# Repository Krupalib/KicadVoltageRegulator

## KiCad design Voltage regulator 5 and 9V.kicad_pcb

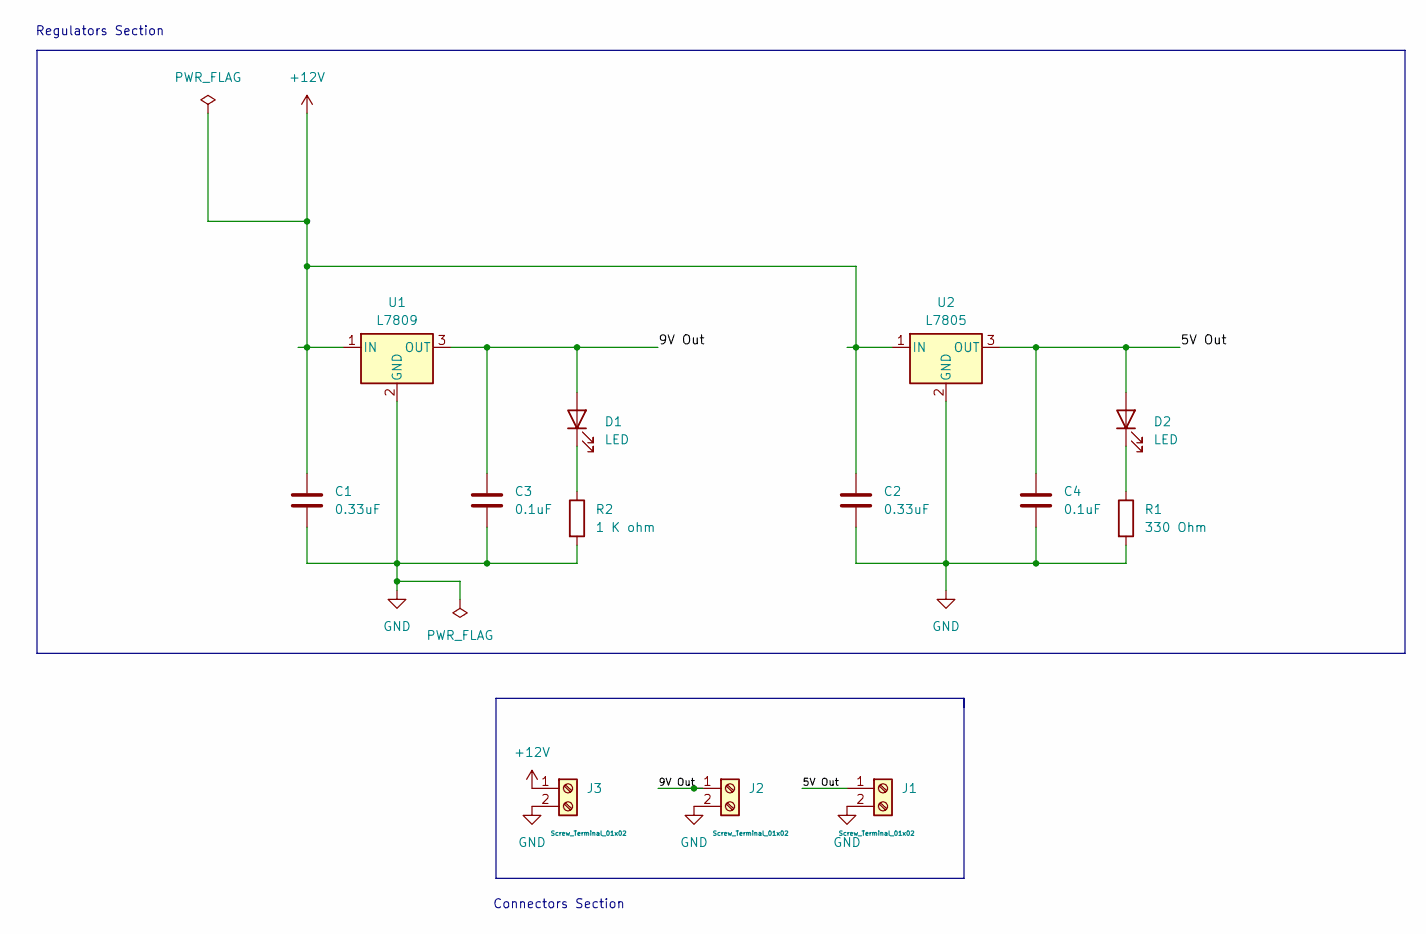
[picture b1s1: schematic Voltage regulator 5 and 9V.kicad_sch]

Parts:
C1, C2: 0.33uF; C_Disc_D4.7mm_W2.5mm_P5.00mm
C3, C4: 0.1uF; C_Disc_D3.0mm_W1.6mm_P2.50mm
D1, D2: LED; LED_D4.0mm
J1, J2, J3: Screw_Terminal_01x02; TerminalBlock_Phoenix_MKDS-1,5-2-5.08_1x02_P5.08mm_Horizont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
R1: 330 Ohm; R_Axial_DIN0204_L3.6mm_D1.6mm_P5.08mm_Horizontal
R2: 1 K ohm; R_Axial_DIN0207_L6.3mm_D2.5mm_P7.62mm_Horizontal
U1: L7809; TO-220-3_Vertical
U2: L7805; TO-220-3_Vertical

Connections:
+12V: C1.1, C2.1, J3.1, U1.1 (IN), U2.1 (IN)
/5V Out: C4.1, D2.2 (A), J1.1, U2.3 (OUT)
/9V Out: C3.1, D1.2 (A), J2.1, U1.3 (OUT)
GND: C1.2, C2.2, C3.2, C4.2, J1.2, J2.2, J3.2, R1.2, R2.2, U1.2 (GND), U2.2 (GND)
unnamed: D1.1 (K), R2.1
unnamed: D2.1 (K), R1.1

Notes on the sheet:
Connectors Section
Regulators Section

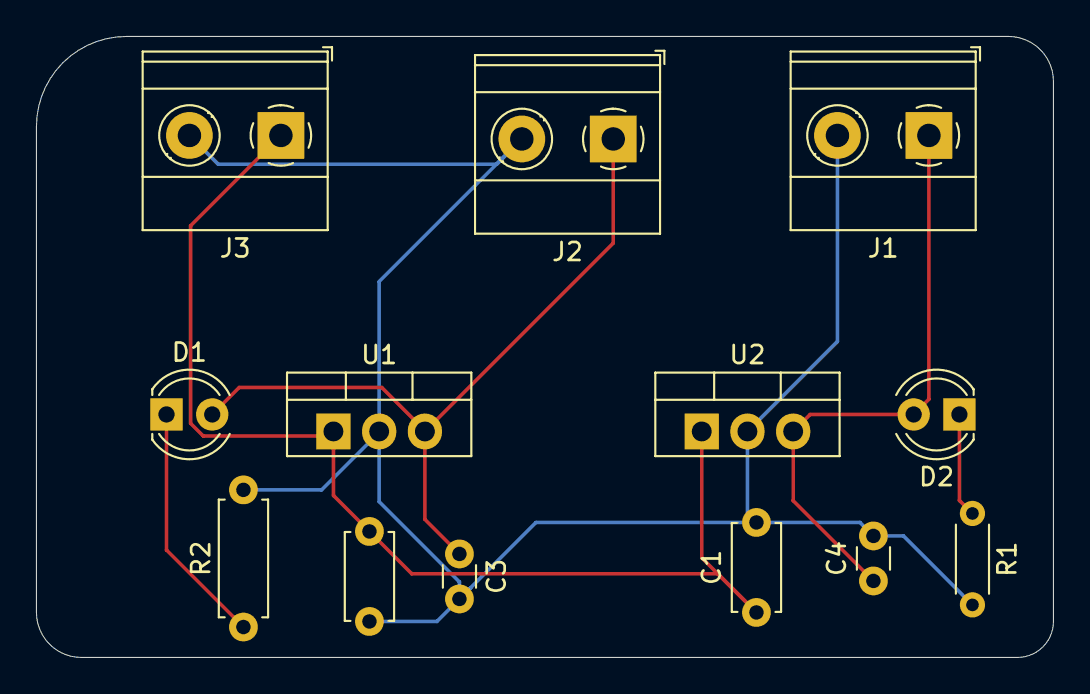
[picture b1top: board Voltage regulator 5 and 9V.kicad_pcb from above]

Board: 2 copper layers, 56.5 x 34.5 mm, 13 parts (0 on the bottom side), 6 nets.

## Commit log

2024-11-06 Initial commit to the project
